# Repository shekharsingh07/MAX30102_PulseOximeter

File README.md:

## **Project Name:** MAX30102 Fingertip Pulse Oximeter

**Table of Contents:**
<ol>
  <li>Description</li>
  <li>License</li>
</ol>

**Description:** <br>For my undergraduate thesis, I designed a PCB for a fingertip Pulse oximeter. The pulse oximeter would use Maxim Integrated's MAX30102 biometric sensor and is created for 24hr monitoring.
<br>The project is divided into two sections:
<ol>
  <li>The embbeded software design:
    <ul>
      <li>Which is further subdivided into sections based on the components - the memory, the I/O system, and the sensor</li>
      <li>The embedded design revolves around the STM32G071RB microcontroller</li>
    </ul>
  </li>
  <li>The PCB design:
    <ul>
      <li>Which contains the necessary files to manufacture this Pulse Oximeter PCB.</li>
    </ul>
  </li>
</ol>

**License:** MIT license

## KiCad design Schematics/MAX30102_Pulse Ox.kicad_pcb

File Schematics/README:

The schematics and PCB designs have been done using KiCAD.

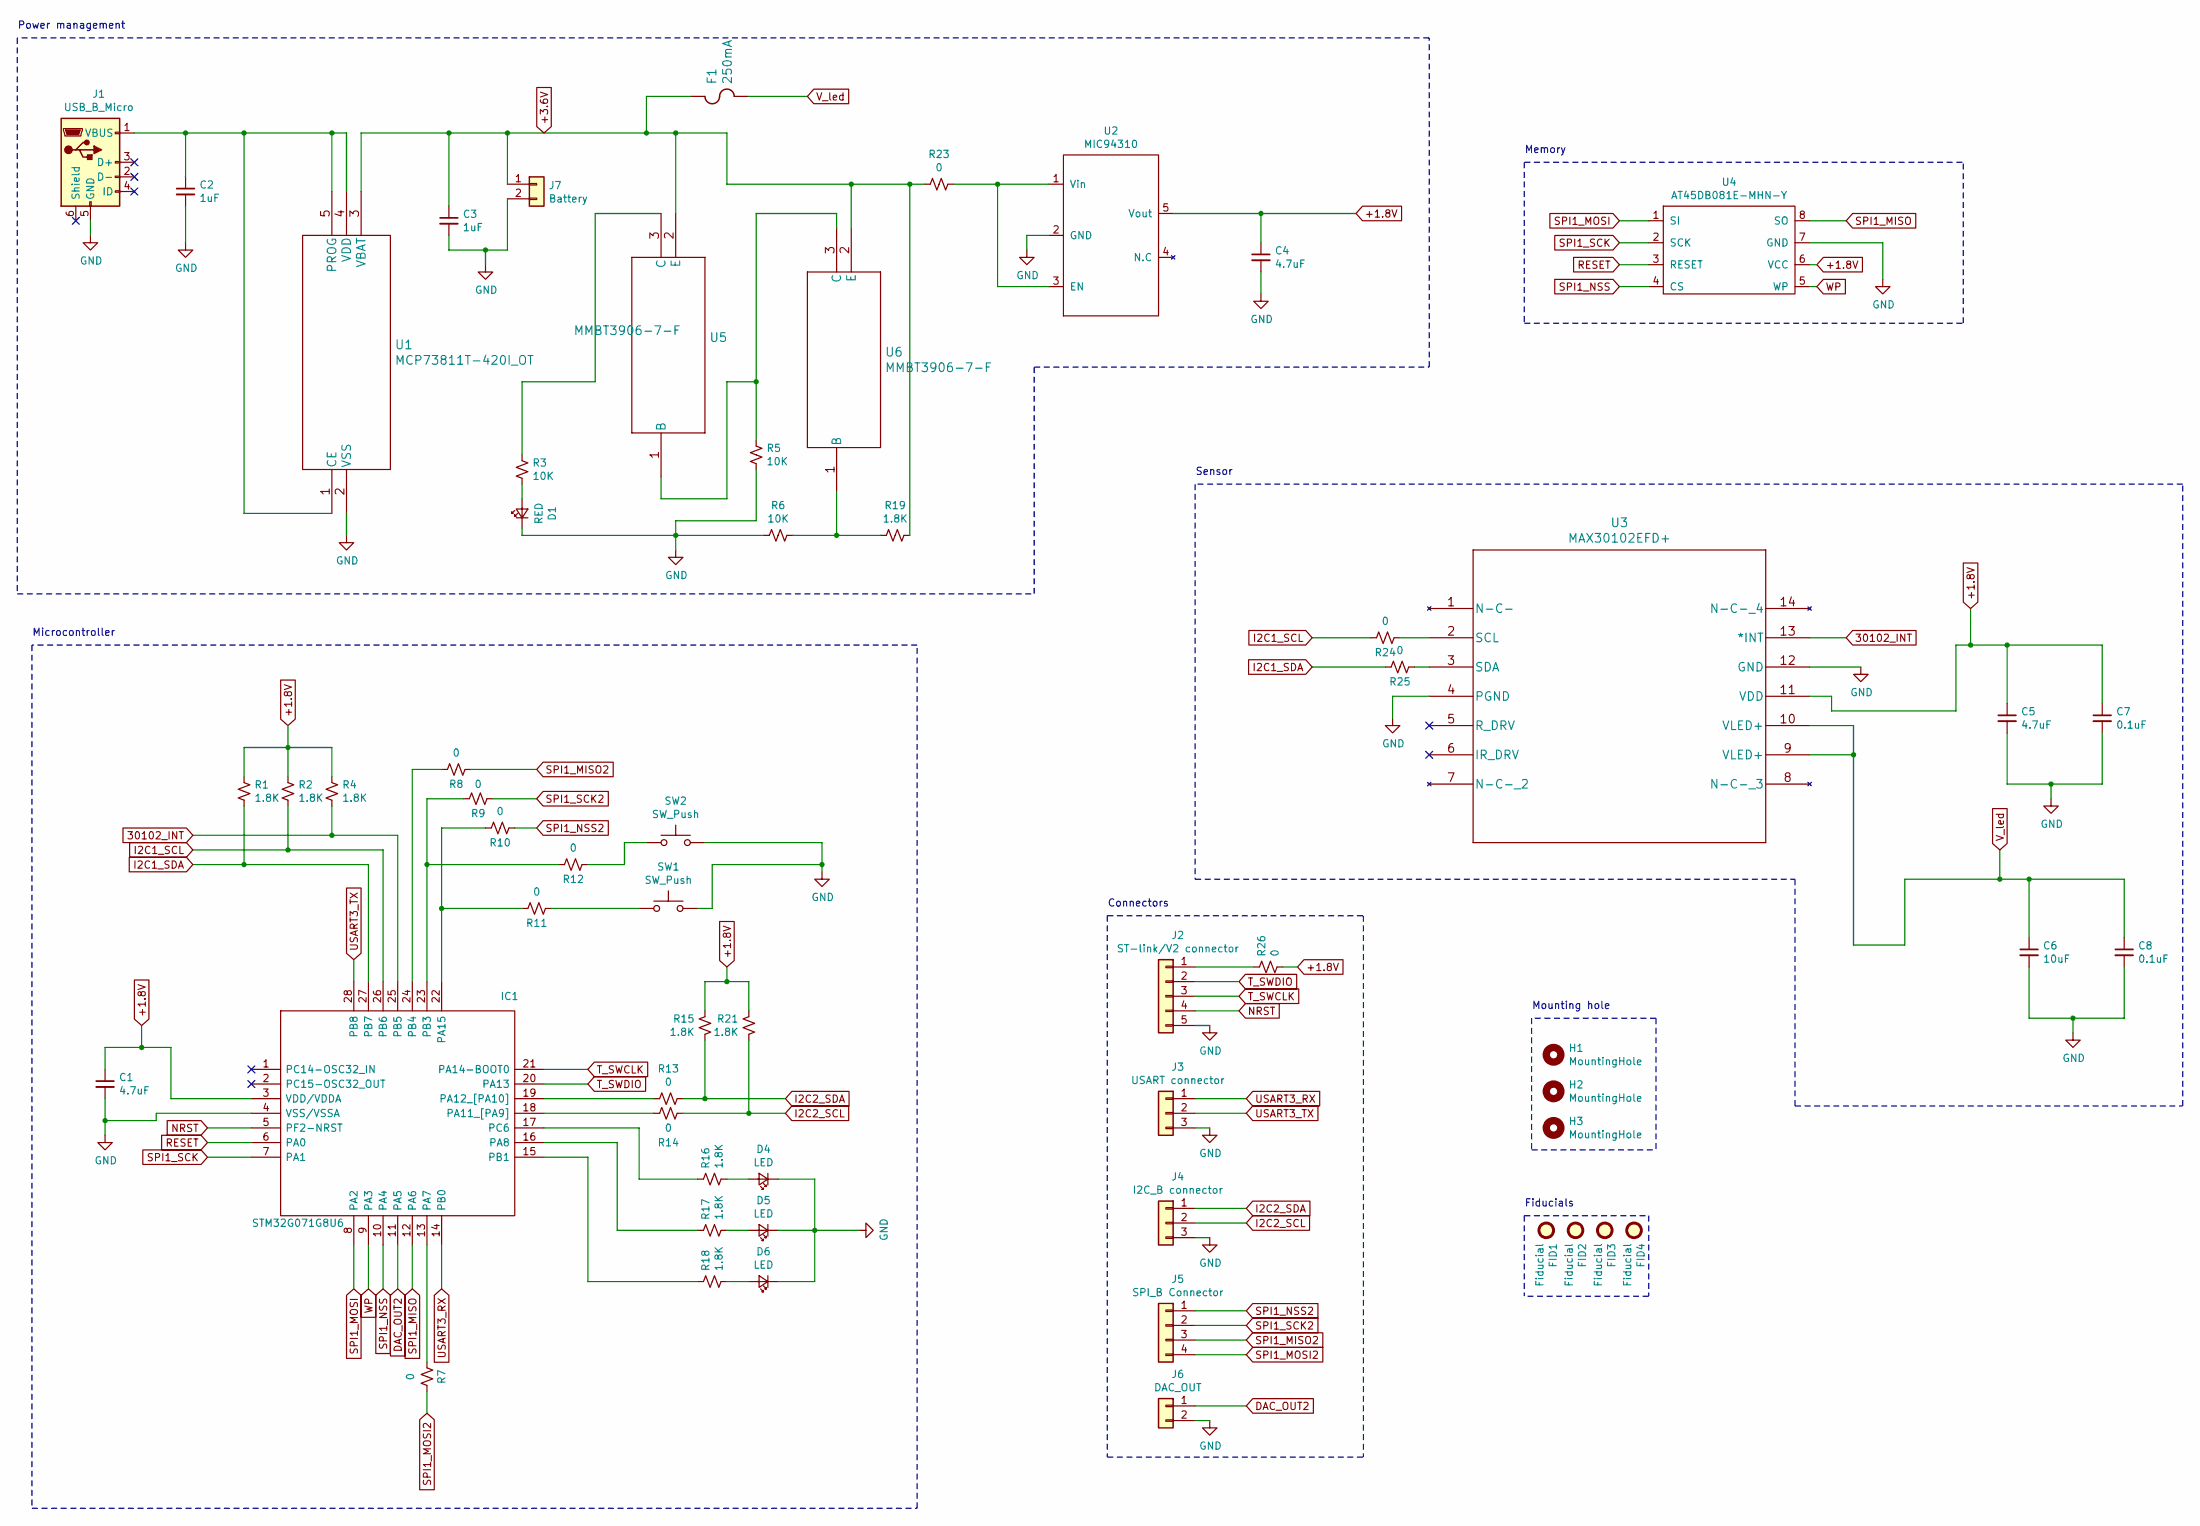
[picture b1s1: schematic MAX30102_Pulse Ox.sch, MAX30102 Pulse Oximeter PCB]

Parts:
C1, C4, C5: 4.7uF; C_0603_1608Metric
C2, C3: 1uF; C_0603_1608Metric
C6: 10uF; C_0603_1608Metric
C7, C8: 0.1uF; C_0603_1608Metric
D1: RED; LED_0603_1608Metric
D4, D5, D6: LED; LED_0603_1608Metric
F1: 250mA; C2Q250
FID1, FID2, FID3, FID4: Fiducial; Fiducial_1mm_Mask2mm
H1, H2, H3: MountingHole; MountingHole_2.1mm
IC1: STM32G071G8U6; STM32G0_UFQFPN28_T1; Manufacturer_Part_Number STM32G071G8U6; Mouser Part Number 511-STM32G071G8U6
J1: USB_B_Micro; USB_Micro-B_Molex_47346-0001
J2: ST-link/V2 connector; SolderWirePad_1x05_SMD
J3: USART connector; SolderWirePad_1x03_SMD
J4: I2C_B connector; SolderWirePad_1x03_SMD
J5: SPI_B Connector; SolderWirePad_1x04_SMD
J6: DAC_OUT; SolderWirePad_1x02_SMD
J7: Battery; SolderWirePad_1x02_SMD
R1, R2, R4, R15, R16, R17, R18, R19, R21: 1.8K; R_0603_1608Metric
R3, R5, R6: 10K; R_0603_1608Metric
R7, R8, R9, R10, R11, R12, R13, R14, R23, R24, R25, R26: 0; R_0603_1608Metric
SW1, SW2: SW_Push; SW_SPST_B3U-1000P
U1: MCP73811T-420I_OT; MCP73811T-420I&slash_OT
U2: MIC94310; MIC94310-GYM5-SOT-753
U3: MAX30102EFD+; MAX30102EFD&plus_
U4: AT45DB081E-MHN-Y; SON127P500X600X60-9N
U5, U6: MMBT3906-7-F

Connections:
30102_INT: IC1.25 (PB5), R4.2, U3.13 (*INT)
+1.8V: C1.1, C4.1, C5.1, C7.1, IC1.3 (VDD/VDDA), R1.1, R2.1, R4.1, R15.1, R21.1, R26.2, U2.5 (Vout), U3.11 (VDD), U4.6 (VCC)
+3.6V: C3.1, F1.2, J7.1, R19.1, R23.2, U1.3 (VBAT), U5.2 (E), U6.2 (E)
DAC_OUT2: IC1.11 (PA5), J6.1
GND: C1.2, C2.2, C3.2, C4.2, C5.2, C6.2, C7.2, C8.2, D1.1 (K), D4.1 (K), D5.1 (K), D6.1 (K), IC1.4 (VSS/VSSA), J1.5 (GND), J2.5, J3.3, J4.3, J6.2, J7.2, R5.2, R6.2, SW1.2, SW2.2, U1.2 (VSS), U2.2 (GND), U3.4 (PGND), U3.12 (GND), U4.7 (GND)
I2C1_SCL: IC1.26 (PB6), R2.2, R24.1
I2C1_SDA: IC1.27 (PB7), R1.2, R25.1
I2C2_SCL: J4.2, R14.2, R21.2
I2C2_SDA: J4.1, R13.2, R15.2
NRST: IC1.5 (PF2-NRST), J2.4
unnamed: C2.1, J1.1 (VBUS), U1.1 (CE), U1.4 (VDD), U1.5 (PROG)
unnamed: D1.2 (A), R3.2
unnamed: D4.2 (A), R16.1
unnamed: D5.2 (A), R17.1
unnamed: D6.2 (A), R18.1
unnamed: IC1.13 (PA7), R7.2
unnamed: IC1.15 (PB1), R18.2
unnamed: IC1.16 (PA8), R17.2
unnamed: IC1.17 (PC6), R16.2
unnamed: IC1.18 (PA11_[PA9]), R14.1
unnamed: IC1.19 (PA12_[PA10]), R13.1
unnamed: IC1.22 (PA15), R10.1, R11.1
unnamed: IC1.23 (PB3), R9.1, R12.1
unnamed: IC1.24 (PB4), R8.1
unnamed: J2.1, R26.1
unnamed: R3.1, U5.3 (C)
unnamed: R5.1, U5.1 (B), U6.3 (C)
unnamed: R11.2, SW1.1
unnamed: R12.2, SW2.1
unnamed: R6.1, R19.2, U6.1 (B)
unnamed: R23.1, U2.1 (Vin), U2.3 (EN)
unnamed: R24.2, U3.2 (SCL)
unnamed: R25.2, U3.3 (SDA)
RESET: IC1.6 (PA0), U4.3 (RESET)
SPI1_MISO: IC1.12 (PA6), U4.8 (SO)
SPI1_MISO2: J5.3, R8.2
SPI1_MOSI: IC1.8 (PA2), U4.1 (SI)
SPI1_MOSI2: J5.4, R7.1
SPI1_NSS: IC1.10 (PA4), U4.4 (CS)
SPI1_NSS2: J5.1, R10.2
SPI1_SCK: IC1.7 (PA1), U4.2 (SCK)
SPI1_SCK2: J5.2, R9.2
T_SWCLK: IC1.21 (PA14-BOOT0), J2.3
T_SWDIO: IC1.20 (PA13), J2.2
USART3_RX: IC1.14 (PB0), J3.1
USART3_TX: IC1.28 (PB8), J3.2
V_led: C6.1, C8.1, F1.1, U3.9 (VLED+), U3.10 (VLED+)
WP: IC1.9 (PA3), U4.5 (WP)

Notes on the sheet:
Microcontroller
Power management
Connectors
Sensor
Memory
Mounting hole
Fiducials

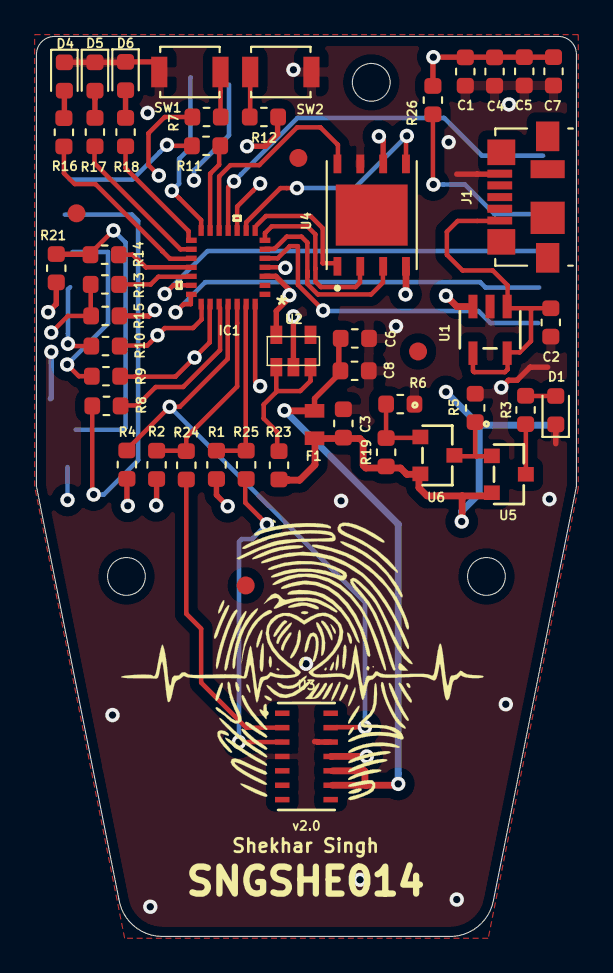
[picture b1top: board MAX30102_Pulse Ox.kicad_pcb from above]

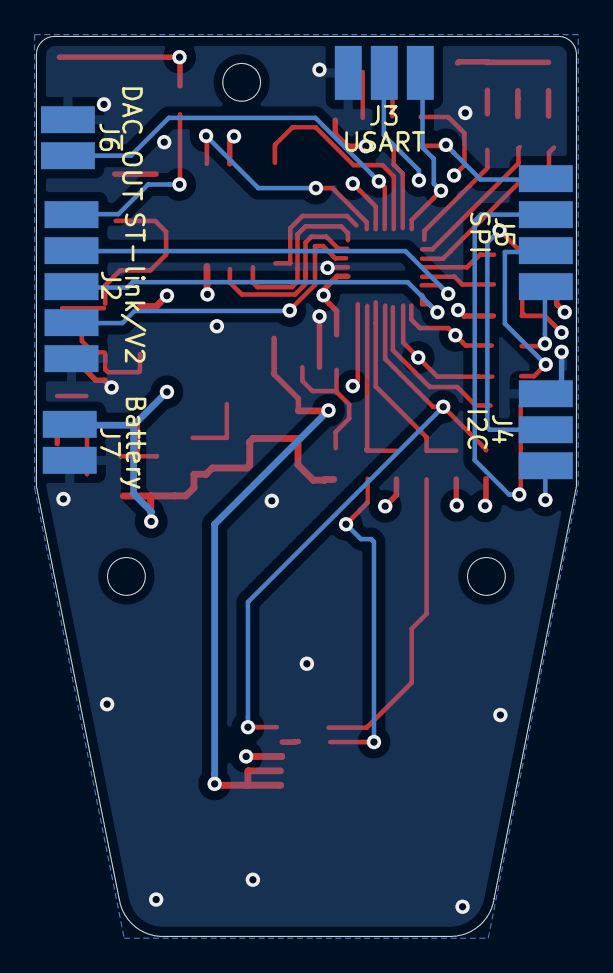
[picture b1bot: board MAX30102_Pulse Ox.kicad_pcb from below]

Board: 4 copper layers, 30.0 x 50.0 mm, 60 parts (6 on the bottom side), 48 nets.

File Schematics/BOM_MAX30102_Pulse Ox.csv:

Id;Designator;Package;Quantity;Designation;Supplier;Reference;Part No.
2;C1,C4,C5;C_0603_1608Metric;3;4.7uF;Digi-Key;https://www.digikey.com/products/en?keywords=1276-1045-1-ND;1276-1045-1-ND
3;C2,C3;C_0603_1608Metric;2;1uF;Digi-Key;https://www.digikey.com/products/en?keywords=1276-1945-1-ND;1276-1945-1-ND
4;C6;C_0603_1608Metric;1;10uF;Digi-Key;https://www.digikey.com/products/en?keywords=1276-1119-1-ND;1276-1119-1-ND
5;C7,C8;C_0603_1608Metric;2;0.1uF;Digi-Key;https://www.digikey.com/products/en?keywords=1276-1935-1-ND;1276-1935-1-ND
6;D1,D4,D5,D6;LED_0603_1608Metric;4;RED;Digi-Key;https://www.digikey.com/products/en?keywords=732-4978-1-ND;732-4978-1-ND
7;F1;C2Q250;1;250mA;Digi-Key;https://www.digikey.com/products/en?keywords=507-1086-1-ND;507-1086-1-ND
10;IC1;STM32G0_UFQFPN28_T1;1;STM32G071G8U6;Digi-Key;https://www.digikey.com/products/en?keywords=497-STM32G071G8U6-ND;497-STM32G071G8U6-ND
11;J1;USB_Micro-B_Molex_47346-0001;1;USB_B_Micro;Digi-Key;https://www.digikey.com/products/en?keywords=609-4613-2-ND;609-4613-2-ND
18;R1,R2,R4,R15,R16,R17,R18,R19,R21;R_0603_1608Metric;9;1.8K;Digi-Key;https://www.digikey.com/products/en?keywords=RMCF0603JT1K80CT-ND;RMCF0603JT1K80CT-ND
19;R3,R5,R6;R_0603_1608Metric;3;10K;Digi-Key;https://www.digikey.com/products/en?keywords=RMCF0603JT10K0CT-ND;RMCF0603JT10K0CT-ND
20;R7,R8,R9,R10,R11,R12,R13,R14,R23,R24,R25,R26;R_0603_1608Metric;12;0;Digi-Key;https://www.digikey.com/products/en?keywords=RMCF0603ZT0R00CT-ND;RMCF0603ZT0R00CT-ND
21;SW1,SW2;SW_SPST_B3U-1000P;2;SW_Push;Digi-Key;https://www.digikey.com/products/en?keywords=SW1020CT-ND;SW1020CT-ND
22;U1;MCP73811T-420I&slash_OT;1;MCP73811T-420I_OT;Digi-Key;https://www.digikey.com/products/en?keywords=MCP73811T-420I%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;MCP73811T-420I/OTCT-ND
23;U2;MIC94310-GYM5-SOT-753;1;MIC94310;Digi-Key;https://www.digikey.com/products/en?keywords=576-4769-1-ND;576-4769-1-ND
24;U3;MAX30102EFD&plus_;1;MAX30102EFD+;Digi-Key;https://www.digikey.com/products/en?keywords=MAX30102EFD%2B-ND;MAX30102EFD+-ND
25;U4;SON127P500X600X60-9N;1;AT45DB081E-MHN-Y;Digi-Key;https://www.digikey.com/products/en?keywords=1265-1110-ND;1265-1110-ND
26;U5,U6;MMBT3906-7-F;2;MMBT3906-7-F;Digi-Key;https://www.digikey.com/products/en?keywords=MMBT3906-FDICT-ND;MMBT3906-FDICT-ND

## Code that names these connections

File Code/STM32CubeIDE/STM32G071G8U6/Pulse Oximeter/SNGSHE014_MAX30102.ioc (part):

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Mcu.Name=STM32G071G(6-8-B)Ux
Mcu.Package=UFQFPN28
Mcu.UserName=STM32G071G8Ux
PA15.GPIOParameters=GPIO_PuPd,GPIO_Label
PA15.GPIO_Label=SW1
PA15.GPIO_PuPd=GPIO_PULLUP
PA15.Signal=GPXTI15
PA8.GPIOParameters=GPIO_PuPd,GPIO_Label
PA8.GPIO_Label=LED2
PA8.GPIO_PuPd=GPIO_PULLUP
PA8.Signal=GPIO_Output
PB0.Mode=Asynchronous
PB0.Signal=USART3_RX
PB1.GPIOParameters=GPIO_PuPd,GPIO_Label
PB1.GPIO_Label=LED3
PB1.GPIO_PuPd=GPIO_PULLUP
PB1.Signal=GPIO_Output
PB3.GPIOParameters=GPIO_PuPd,GPIO_Label
PB3.GPIO_Label=SW2
PB3.GPIO_PuPd=GPIO_PULLUP
PB3.Signal=GPXTI3
PB4.Signal=GPIO_Output
PB5.GPIOParameters=GPIO_PuPd,GPIO_Label
PB5.GPIO_Label=INT
PB5.GPIO_PuPd=GPIO_PULLUP
PB5.Signal=GPXTI5
PB6.GPIOParameters=GPIO_Label
PB6.GPIO_Label=SCL
PB6.Mode=I2C
PB6.Signal=I2C1_SCL
PB7.GPIOParameters=GPIO_Label
PB7.GPIO_Label=SDA
PB7.Mode=I2C
PB7.Signal=I2C1_SDA
PB8.Mode=Asynchronous
PB8.Signal=USART3_TX
PC6.GPIOParameters=GPIO_Label
PC6.GPIO_Label=LED1
PC6.Signal=GPIO_Output
RCC.HSE_VALUE=8000000
RCC.SYSCLKFreq_VALUE=16000000
board=custom

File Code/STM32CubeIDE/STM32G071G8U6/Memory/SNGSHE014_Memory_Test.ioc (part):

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Mcu.Name=STM32G071G(6-8-B)Ux
Mcu.Package=UFQFPN28
Mcu.UserName=STM32G071G8Ux
PA0.GPIOParameters=GPIO_Label
PA0.GPIO_Label=RESET
PA0.Signal=GPIO_Output
PA1.Mode=Full_Duplex_Master
PA1.Signal=SPI1_SCK
PA2.Mode=Full_Duplex_Master
PA2.Signal=SPI1_MOSI
PA3.GPIOParameters=GPIO_Label
PA3.GPIO_Label=WP
PA3.Signal=GPIO_Output
PA4.Mode=NSS_Signal_Hard_Output
PA4.Signal=SPI1_NSS
PA6.Mode=Full_Duplex_Master
PA6.Signal=SPI1_MISO
PB0.Mode=Asynchronous
PB0.Signal=USART3_RX
PB8.Mode=Asynchronous
PB8.Signal=USART3_TX
RCC.HSE_VALUE=8000000
RCC.SYSCLKFreq_VALUE=16000000
board=custom

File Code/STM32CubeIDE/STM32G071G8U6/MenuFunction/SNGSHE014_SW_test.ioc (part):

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Mcu.Name=STM32G071G(6-8-B)Ux
Mcu.Package=UFQFPN28
Mcu.UserName=STM32G071G8Ux
PA13.Mode=Serial_Wire
PA13.Signal=SYS_SWDIO
PA14-BOOT0.Mode=Serial_Wire
PA14-BOOT0.Signal=SYS_SWCLK
PA15.GPIOParameters=GPIO_PuPd,GPIO_Label,GPIO_ModeDefaultEXTI
PA15.GPIO_Label=SW1
PA15.GPIO_ModeDefaultEXTI=GPIO_MODE_IT_RISING_FALLING
PA15.GPIO_PuPd=GPIO_PULLUP
PA15.Signal=GPXTI15
PA4.Mode=SYS_WakeUp1
PA4.Signal=SYS_WKUP2
PA8.GPIOParameters=PinState,GPIO_PuPd,GPIO_Label
PA8.GPIO_Label=LED1
PA8.GPIO_PuPd=GPIO_PULLUP
PA8.PinState=GPIO_PIN_RESET
PA8.Signal=GPIO_Output
PB0.Mode=Asynchronous
PB0.Signal=USART3_RX
PB1.GPIOParameters=GPIO_PuPd,GPIO_Label
PB1.GPIO_Label=LED2
PB1.GPIO_PuPd=GPIO_PULLUP
PB1.Signal=GPIO_Output
PB3.GPIOParameters=GPIO_PuPd,GPIO_Label,GPIO_ModeDefaultEXTI
PB3.GPIO_Label=SW2
PB3.GPIO_ModeDefaultEXTI=GPIO_MODE_IT_RISING_FALLING
PB3.GPIO_PuPd=GPIO_PULLUP
PB3.Signal=GPXTI3
PB8.Mode=Asynchronous
PB8.Signal=USART3_TX
PC14-OSC32_IN\ (PC14).Mode=LSE-External-Oscillator
PC14-OSC32_IN\ (PC14).Signal=RCC_OSC32_IN
PC15-OSC32_OUT\ (PC15).Mode=LSE-External-Oscillator
PC15-OSC32_OUT\ (PC15).Signal=RCC_OSC32_OUT
RCC.HSE_VALUE=8000000
RCC.SYSCLKFreq_VALUE=16000000
board=custom

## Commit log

2020-10-17 Add files via upload
    KiCAD project files
2020-10-17 Create Menu_Function
2020-10-17 Add files via upload
    Uploaded the code for the menu functions
2020-10-18 Add files via upload
    Updated the menu UI
2020-11-10 Create STM32G071x_MAX30102 sensor
2020-11-10 Create pushbuttons
2020-11-10 Create MAX30102
2020-11-10 Add files via upload
    The project folders for the MAX30102 sensor
2020-11-10 Add files via upload
    The project files for the menu functions
2020-11-10 Create memory

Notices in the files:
parts and their libraries:
Copyright 2016 Accelerated Designs. All rights reserved.
